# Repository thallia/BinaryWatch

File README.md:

# BinaryWatch
My first project designing and creating *everything*. 

Current board rev: *4.1*

Supplies I went through for breadboard testing:
  * atmega328p-pu
  * sn74hc595n x2
  * LEDs x10 
  * 16MHz external crystal
  * 32.768kHz external crystal
  * 2 22pF capacitors
  * 2 0.1uF capacitors
  * two buttons for configuring time
  * one button for sleep/wakeup
  * jumper wires
  
  * arduino uno (for easier programming in the beginning)
  
Supplies for PCB:
  * (SMD) atmega328p-au 
  * 74hc595 SMD shift registers x2
  * JST right angle connector
  * 400mAh Li-Po battery
  * LEDs 1206 SMD x10 (or flat top, whatever you prefer.)
  * 32.768kHz SC-32S SMD crystal
  * SMD capacitors 0805 22pF x2
  * SMD capacitors 0805 12.5pF x2
  * 3 buttons
  * 10k SMD resistors 0805 x1
  * 2k SMD resistors 0805 x10 (in testing for LED brightness)
  * PCB (oshpark)
  * 3D printed case (fusion360)

**PCB designed on:** eagleCAD

**3D case designed on:** fusion360

**CURRENT TASK:** This project is complete!

Blog Posts following development:

**Basis:**  https://thalliatree.wordpress.com/2017/12/25/74hc595-texas-instruments-shift-registers/

**Intro:**  https://thalliatree.wordpress.com/2018/01/01/project-hype-binary-wristwatch/

**Breadboard Hardware (with Uno):**   https://thalliatree.wordpress.com/2018/01/26/atmega328p-microcontroller-74hc595-shift-register-setup-and-test-binary-watch/

**Code - Part 1:**  https://thalliatree.wordpress.com/2018/01/29/code-part-1-binary-watch/

**Code - Part 2:**  https://thalliatree.wordpress.com/2018/01/31/code-part-2-binary-watch/

**Breadboard Hardware (without Uno):**    https://www.thalliatree.net/posts/prepping-the-atmega-hardware-test-bw.html

**Mock Up PCB with coin cells + early schematic:**   https://thalliatree.wordpress.com/2018/02/05/mock-up-pcb-binary-watch/

**Code - Part 3:**   https://thalliatree.wordpress.com/2018/03/16/code-part-3-binary-watch/

**Atmega328p 32.768kHz, sleep modes, and new schematic:**   https://thalliatree.wordpress.com/2018/03/26/atmega328p-32-768khz-sleep-modes-and-new-schematic-binary-watch/

**Final Code, Schematic, and PCB layout:**   https://thalliatree.wordpress.com/2018/04/03/final-code-schematic-and-pcb-binary-watch/

**PCB 95% Complete:**   https://thalliatree.wordpress.com/2018/05/03/pcb-95-complete-binary-watch/

**Binary Watch | Complete:**  https://thalliatree.wordpress.com/2018/05/14/binary-watch-complete

For later revisions: 
-  Power: The charging and power circuit needs to be on the board itself. That way I can charge it and not have to worry about buying a bunch of LiPo batteries over and over.
- Experimenting with new power: I want to try powering this thing from a coin cell again. I have 2 other boards with this design, so I'm going to solder them together, but with different resistor types on the LEDs to see how much current the LEDs and microcontroller are drawing. That way I can estimate what the best resistor value is for brightness + mAh value of battery to get.
- The 3D case is cool with the PCB exposed, but it ain't cool because it's exposed to the weather and other wet and sticky things. Therefore I must cover it up. The lid for case I design next will likely be screwed on, 1) for easier access and 2) for better security of the PCB. Depending on how secure I want it, I may add some kind of sealant. We'll see...
- 3D case: If I add a charging port, it'll need a hole for the plug.
- Through-hole LEDs: if the PCB is to be covered by the case, SMD LEDs aren't going to shine through very well. I have some cool cylindrical blue LEDs that should work, so I'll have to design the case cover to sit around/on top of them, which requires a new PCB design entirely.
- With the PCB case covering the top, I'll need to either add holes for the pushbuttons or design a way to put them on the sides of the case.
- Watch strap: I'm planning on weaving some leather cord in a celtic knot fashion, or maybe some cool braided thing. I've been looking at some chunkier weaves on Pinterest, but I haven't found the right one yet.
- With the new case top, I may make it thicker and engrave some cool circuit-looking designs around the LEDs poking through and paint the engravings an electric blue color. Electric blue is a great idea.

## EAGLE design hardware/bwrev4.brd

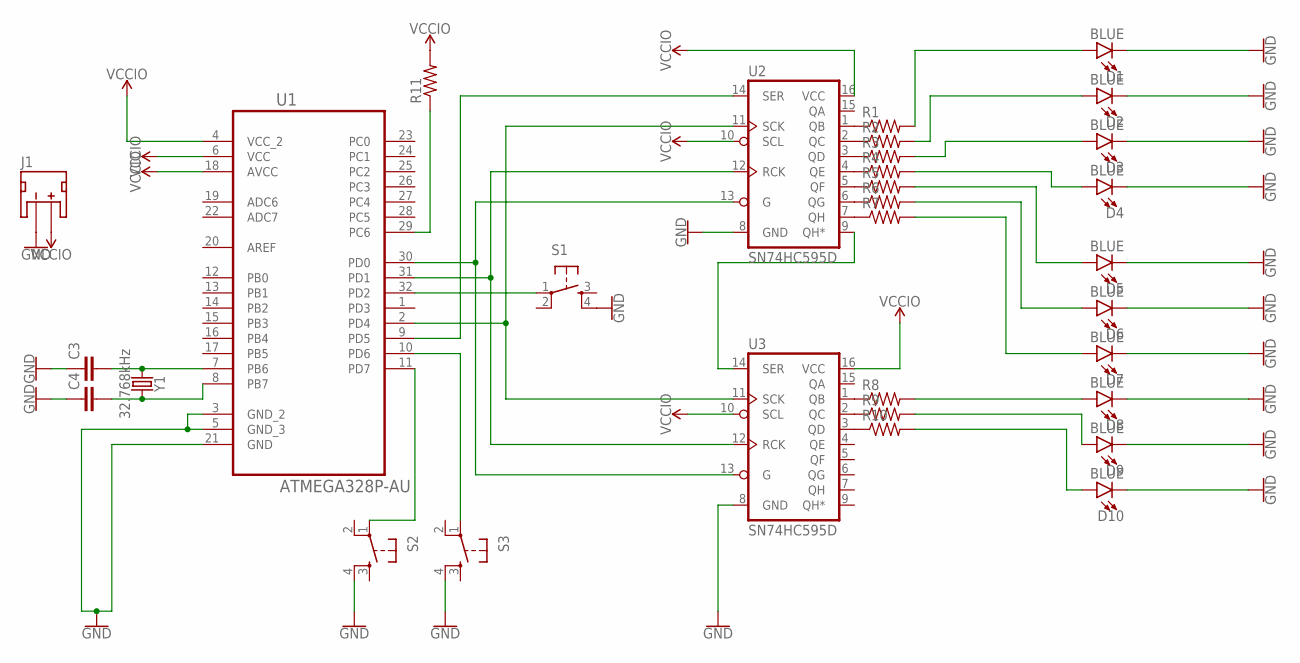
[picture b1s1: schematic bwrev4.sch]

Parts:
C3, C4: C-EUC0805; C0805
D1, D2, D3, D4, D5, D6, D7, D8, D9, D10: BLUE; LED-1206
J1: JST_2MM_MALE; JST-2-SMD
R1, R2, R3, R4, R5, R6, R7, R8, R9, R10, R11: R-US_M0805; M0805
S1, S2, S3: TAC_SWITCHPTH; TACTILE-PTH
U1: ATMEGA328P-AU; QFP80P900X900X120-32N
U2, U3: SN74HC595D; SO16
Y1: 32.768kHz; CRYSTAL-SMD-3.2X1.5MM

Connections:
GND: C3.1, C4.1, D1.C, D2.C, D3.C, D4.C, D5.C, D6.C, D7.C, D8.C, D9.C, D10.C, J1.1 (-), S1.4, S2.4, S3.4, U1.3 (GND_2), U1.5 (GND_3), U1.21 (GND), U2.8 (GND), U3.8 (GND)
unnamed: S1.1, U1.32 (PD2)
unnamed: R1.1, U2.1 (QB)
unnamed: R2.1, U2.2 (QC)
unnamed: R3.1, U2.3 (QD)
unnamed: R4.1, U2.4 (QE)
unnamed: R5.1, U2.5 (QF)
unnamed: R6.1, U2.6 (QG)
unnamed: R7.1, U2.7 (QH)
unnamed: R8.1, U3.1 (QB)
unnamed: R9.1, U3.2 (QC)
unnamed: S3.1, U1.10 (PD6)
unnamed: C4.2, U1.8 (PB7), Y1.P$2 (2)
unnamed: C3.2, U1.7 (PB6), Y1.P$1 (1)
unnamed: R10.1, U3.3 (QD)
unnamed: D4.A, R4.2
unnamed: D5.A, R5.2
unnamed: D1.A, R1.2
unnamed: D2.A, R2.2
unnamed: D3.A, R3.2
unnamed: D6.A, R6.2
unnamed: D7.A, R7.2
unnamed: D8.A, R8.2
unnamed: D9.A, R9.2
unnamed: D10.A, R10.2
unnamed: U2.9 (QH*), U3.14 (SER)
unnamed: U1.30 (PD0), U2.13 (G), U3.13 (G)
unnamed: U1.9 (PD5), U2.14 (SER)
unnamed: U1.31 (PD1), U2.12 (RCK), U3.12 (RCK)
unnamed: U1.2 (PD4), U2.11 (SCK), U3.11 (SCK)
unnamed: R11.1, U1.29 (PC6)
unnamed: S2.1, U1.11 (PD7)
VCCIO: J1.2 (+), R11.2, U1.4 (VCC_2), U1.6 (VCC), U1.18 (AVCC), U2.10 (SCL), U2.16 (VCC), U3.10 (SCL), U3.16 (VCC)

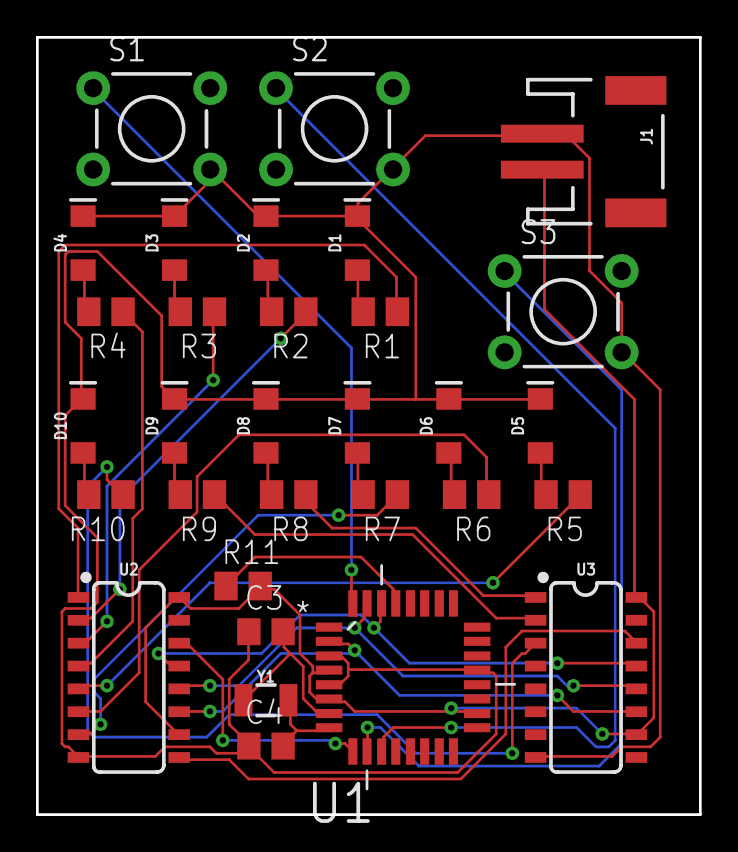
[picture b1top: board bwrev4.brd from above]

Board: 2 copper layers, 36.8 x 43.2 mm, 31 parts (0 on the bottom side), 33 nets.

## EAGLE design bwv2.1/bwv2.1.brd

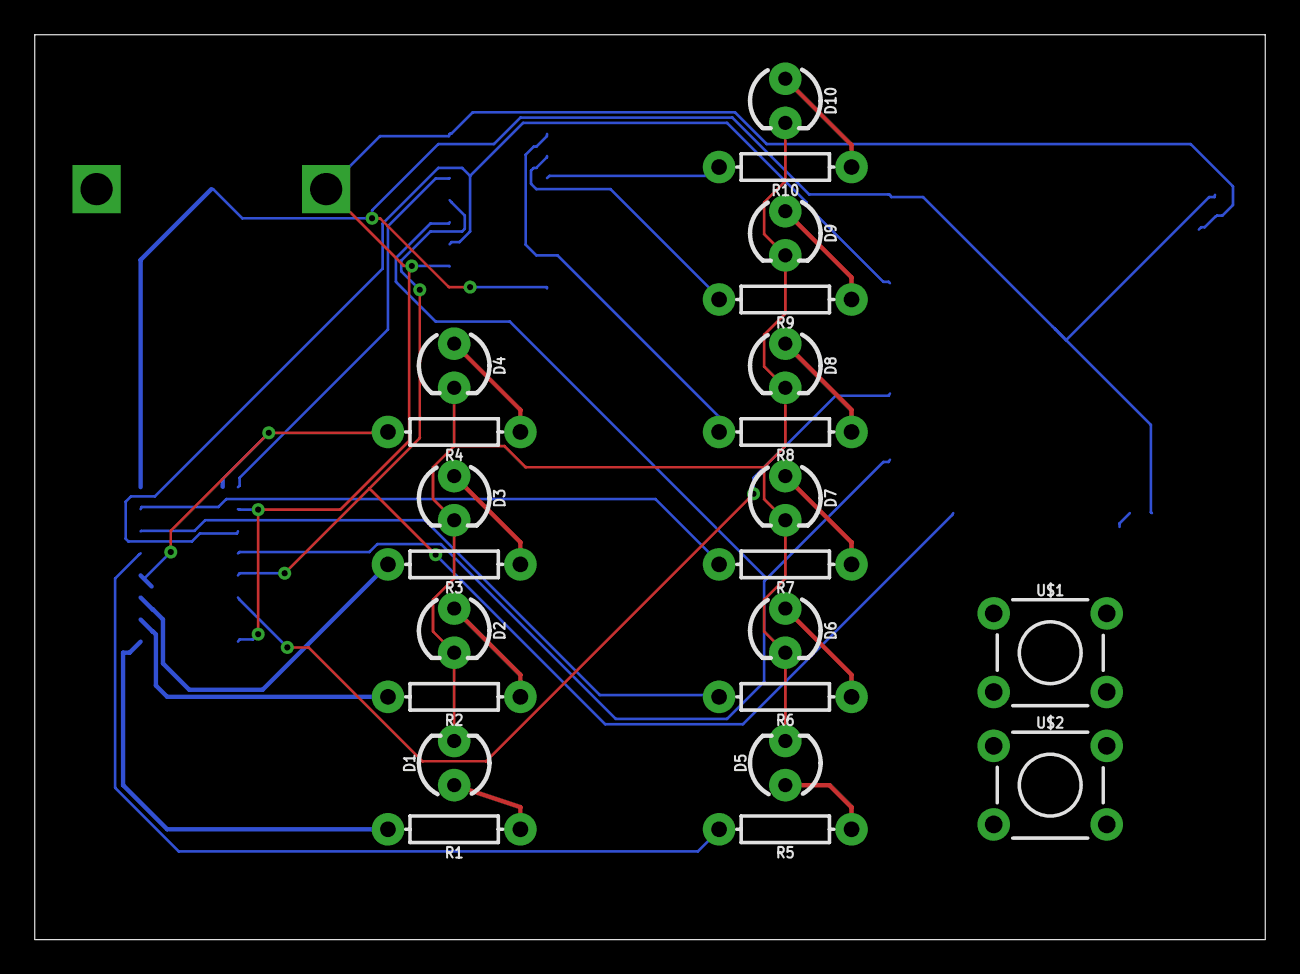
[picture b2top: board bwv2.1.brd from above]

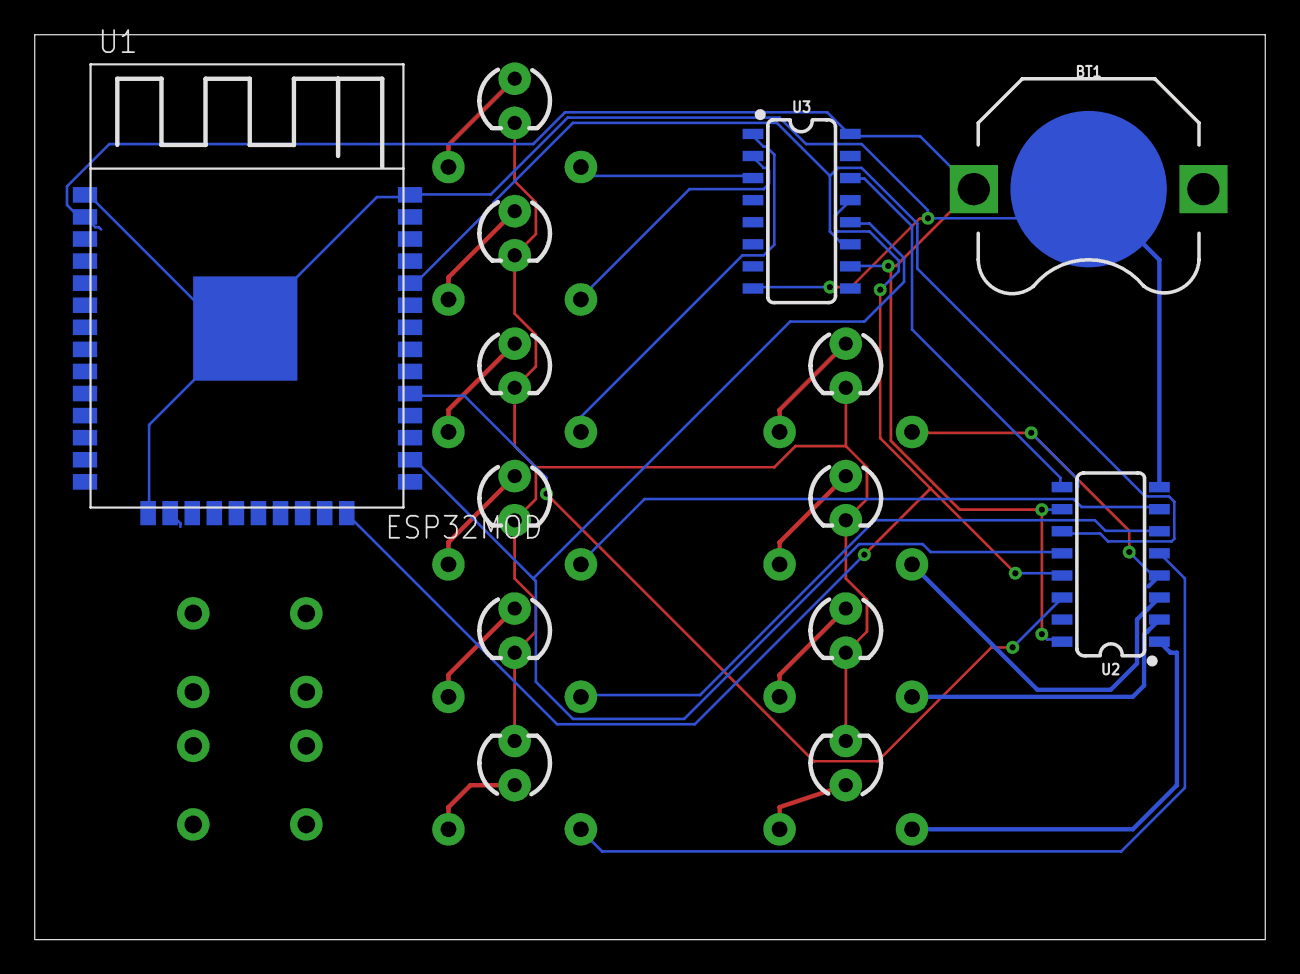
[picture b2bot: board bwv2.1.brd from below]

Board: 2 copper layers, 70.8 x 52.1 mm, 26 parts (4 on the bottom side), 28 nets.

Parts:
BT1: BATTCON_12MM_PTH
D1, D2, D3, D4, D5, D6, D7, D8, D9, D10: LED_3MM
R1, R2, R3, R4, R5, R6, R7, R8, R9, R10: 330; AXIAL-0.3
U1: ESP32MOD
U2, U3: SN74HC595D; SO16
U$1, U$2: TACTILE_SWITCH_PTH_6.0MM

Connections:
GND: BT1.GND, U1.0, U1.1, U1.15, U1.38, U2.8, U3.8
unnamed: U1.24, U2.13, U3.13
unnamed: U1.26, U2.12, U3.12
unnamed: U1.34, U2.11, U3.11
unnamed: U1.29, U2.14
unnamed: D1.K, D2.K, D3.K, D4.K, D5.K, D6.K, D7.K, D8.K, D9.K, D10.K
unnamed: U2.9, U3.14
unnamed: D1.A, R1.P$1
unnamed: R1.P$2, U2.1
unnamed: D2.A, R2.P$1
unnamed: R2.P$2, U2.2
unnamed: D6.A, R6.P$1
unnamed: D3.A, R3.P$1
unnamed: D4.A, R4.P$1
unnamed: R3.P$2, U2.3
unnamed: R4.P$2, U2.4
unnamed: D5.A, R5.P$1
unnamed: R5.P$2, U2.5
unnamed: R6.P$2, U2.6
unnamed: R7.P$2, U2.7
unnamed: D7.A, R7.P$1
unnamed: D8.A, R8.P$1
unnamed: D9.A, R9.P$1
unnamed: D10.A, R10.P$1
unnamed: R8.P$2, U3.1
unnamed: R9.P$2, U3.2
unnamed: R10.P$2, U3.3
unnamed: BT1.VCC@1, U1.2, U2.10, U2.16, U3.10, U3.16

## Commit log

2018-01-03 added eagleCAD gerber and board files for rev2.1
2018-01-28 added initial binary watch rev 1 code
    It's in good standing, it works, albeit slightly better than how Gector's reacted on my atmega. I altered the minute function, but it's
    still acting up, so that will be the next thing to fix.
2018-01-28 added gector's original code with my comments explaining what things do for learning purposes
2018-01-29 fixed the minute portion of the code
    replaced the if(millis() - lastTick) with the correct stuff, turns out that had been goofing the whole thing up. Now onto deep sleep.
2018-01-30 solved why minutes won't go to 59 had to add else's to the IF functions for the buttons. Now to find out why they aren't receiving input, and why having both checkHour and checkMin causes some sort o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
2018-01-31 modified the inHour and inMinute to be input and activated the pullup resistors
2018-01-31 fixed the pullup resistor code, it works with the arduino uno!
2018-01-31 updated README to most recent additions, current task, and list of blog post documentation of process
2018-01-31 fixed spacing in links
2018-01-31 added the correct pinout of ATMega --> shift register, and shift register I/O to LED number
2018-01-31 fixed spacing
2018-01-31 bolded the important things
2018-02-04 added rest of pins to connect to to make circuit work
2018-02-04 added rest of pins to connect to to make circuit work - oops forgot caps
2018-02-04 added next steps and updated documentation log with new post
2018-02-04 we don't want that file
2018-02-04 schematic from EasyEDA for scholarship; going to redo in eagleCAD. Document.
2018-02-05 updated with most recent hardware post, next steps feb 4, 2018
2018-02-08 added note
2018-03-13 cleaned up the bclock and replaced with bwatch. Bwatch is where i'm gonna test all the disabled modules.
2018-03-14 added backup of working/cleaned file while testing the disabled modules on bwatch2-0.cpp
2018-03-14 added disabled modules - UNTESTED
2018-03-14 updated README with links, next steps. Moved working code to src/
2018-03-15 added bwatch rev 3, with all the untested RTC and sleep mode crud.
2018-03-15 updated new task
2018-03-15 typo
2018-03-16 added new RTC modules, everything compiles so lets hope it works when the hardware comes in.
2018-03-16 updated task, PCB supplies, cleaned up code.
2018-03-16 added test file with disabling modules in the hardware and setting up RTC hardware wise instead of using a DS1307
2018-03-18 debugging the bwatch and added the testing khz clock from stack exchange.
2018-03-18 don't need that file anymore
2018-03-18 oops forgot to delete these too
2018-03-18 updated pins, clocks, and decoupling caps
2018-03-18 added new blog post documentation
2018-03-23 added engineering log, updated README.
2018-03-25 figured out the sleep modes and fuse bytes!
2018-03-26 working code w/ 32.786kHz clock! buttons untested.
2018-03-26 made directory for hardware design and documentation.
2018-03-26 working code(32kHz) minus the buttons.
2018-03-26 eagle cad schematic rev3-1
2018-03-26 ugly final schematic
2018-03-26 updated tasks.
2018-03-29 updated with new tasks.
2018-03-29 Added new blog post.
2018-03-30 testing files for new hardware + pin changes.
2018-04-01 fixed time changing buttons in code, added updated hardware pins.
2018-04-01 new task.
2018-04-01 final schematic and PCB layout.
2018-04-03 new task, FINAL CODE!
2018-04-03 FINAL CODE
2018-04-03 moved testing files.
2018-04-09 fusion360 STL files.
2018-05-08 Revised the 3D case to more efficient for using
2018-05-08 Added newest blog posts and updated links.
2018-05-08 updated lid to be slightly more covering.
2018-05-12 fixed layout
2018-05-12 organized files to be more accessible
2018-05-16 finished work
    added finished status, last blog post, and later revisions goals.

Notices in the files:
parts and their libraries:
SparkFun-Batteries: Licensing: Creative Commons ShareAlike 4.0 International - https://creativecommons.org/licenses/by-sa/4.0
